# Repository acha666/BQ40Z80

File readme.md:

# BQ40Z80

一个简单的BQ40Z80 Demo板，~~绘制~~测试中

# 参考资料

* [bq4050从上电到PF](https://bq4050startup.vercel.app/)

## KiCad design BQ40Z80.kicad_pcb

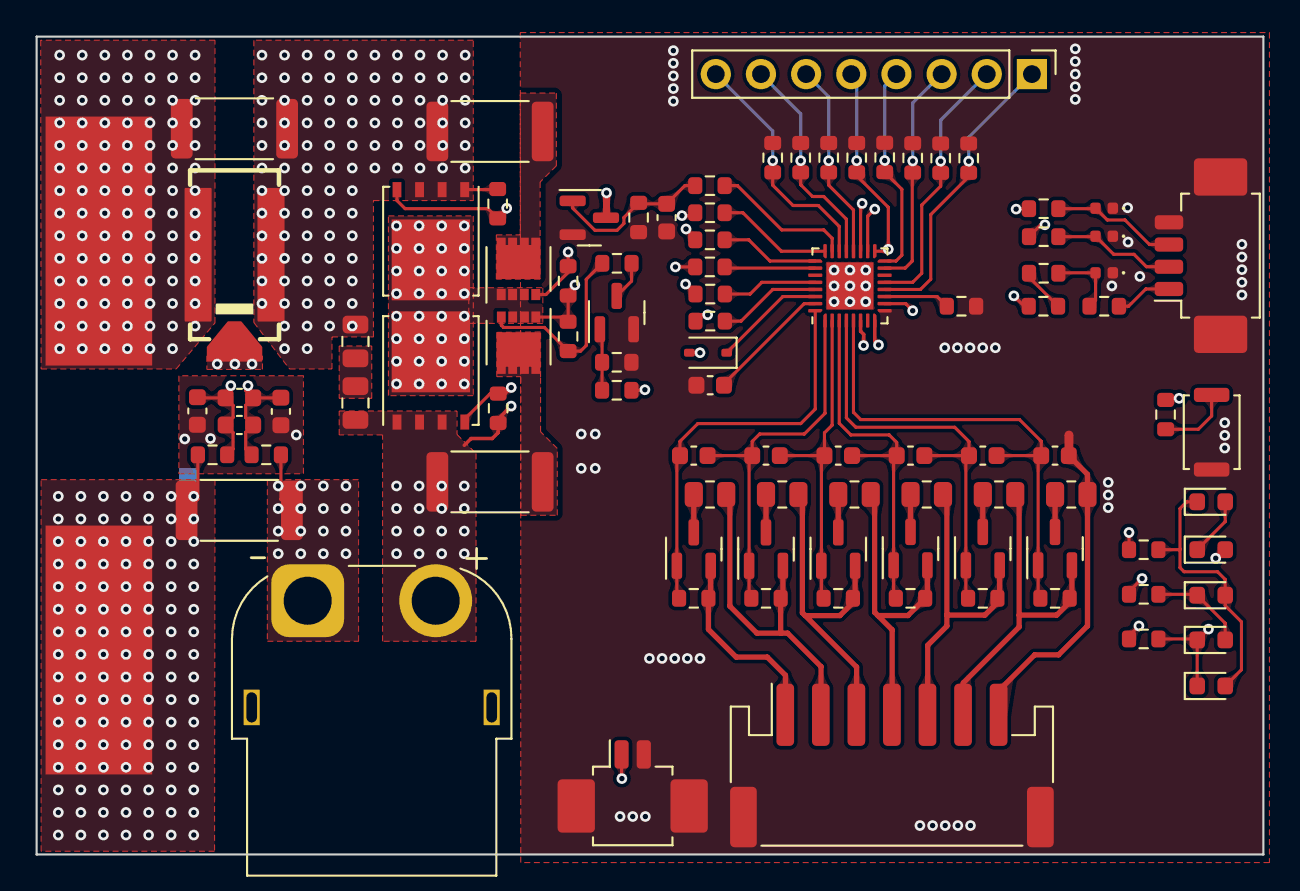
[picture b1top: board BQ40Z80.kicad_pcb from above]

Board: 4 copper layers, 69.0 x 46.0 mm, 97 parts (0 on the bottom side), 69 nets.

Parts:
C1, C2, C3, C4, C5, C6, C7, C13: 100nF; C_0603_1608Metric
C8: 2.2uF; C_0603_1608Metric
C9, C11: 100nF; C_0805_2012Metric
C10, C14: NC; C_0603_1608Metric
C12: 100pF; C_0603_1608Metric
D1: 1N5819WS; D_SOD-323
D2, D3, D4: D_TVS; D_0402_1005Metric
D5, D6, D7, D8, D9: LED; LED_0603_1608Metric
F1: SFK-3045; FUSE-SMD_3P-L9.5-W5.0
J1: Conn_01x02; Molex_PicoBlade_53261-0271_1x02-1MP_P1.25mm_Horizontal
J2: Conn_01x03; Molex_PicoBlade_53261-0471_1x04-1MP_P1.25mm_Horizontal
J3: Conn_01x07_MountingPin; JST_PH_S7B-PH-SM4-TB_1x07-1MP_P2.00mm_Horizontal
J4: Conn_01x08; PinHeader_1x08_P2.54mm_Vertical
J5: Conn_01x02_MountingPin; AMASS_XT60PW-F_1x02_P7.20mm_Horizontal
NT1: NetTie_2; NetTie-2_SMD_Pad0.5mm
NT2: NetTie_2; NetTie-2-234Layers_SMD_Pad0.5mm
Q1, Q2, Q3, Q4, Q5, Q6: AO3401A; SOT-23
Q7: DMN6075S; SOT-23
Q8, Q12: CSD18540Q5B; TDSON-8-1
Q9, Q10: AON6411; VSON-8_3.3x3.3mm_P0.65mm_NexFET
Q11: 2N7002; SOT-23
R1, R2, R3, R4, R5, R6: 43R; R_0805_2012Metric
R7, R8, R9, R10, R11, R12, R38, R49: 1K; R_0603_1608Metric
R13: 0R/NC; R_2512_6332Metric
R14, R15, R18, R19, R27: 5.1K; R_0603_1608Metric
R16, R20, R23, R25, R28, R30: 10M; R_0603_1608Metric
R17, R29: 100R/2W; R_2512_6332Metric
R21, R22, R26: 100R; R_0603_1608Metric
R24: 3mR; R_2512_6332Metric
R31, R32, R33, R34, R36, R37, R39, R40: 0R; R_0603_1608Metric
R35, R41, R42: 200R; R_0603_1608Metric
R43, R44, R45, R46, R47, R48: NC; R_0603_1608Metric
SW1: SW_Push; SW_Push_SPST_NO_Alps_SKRK
TH1: 10K@25°C; R_0603_1608Metric
TP1: BAT+; SolderWirePad_1x01_SMD_14x6mm
TP11: BAT-; SolderWirePad_1x01_SMD_14x6mm
U1: BQ40Z80RSMR; QFN-32-1EP_4x4mm_P0.4mm_EP2.65x2.65mm

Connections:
/0.0V: C6.2, J3.7, NT1.1, R6.2
/4.2V: J3.6, Q6.2 (S), R5.2, R12.1
/8.4V: J3.5, Q5.2 (S), R4.2, R11.1
/12.6V: J3.4, Q4.2 (S), R3.2, R10.1
/16.8V: J3.3, Q3.2 (S), R2.2, R9.1
/21.0V: J3.2, Q2.2 (S), R1.2, R8.1
/25.2V: J3.1, Q1.2 (S), R7.1
/BAT+: D1.2 (A), F1.1, R13.1, TP1.1
/CHG: R18.2, U1.29 (CHG)
/DISP: R46.2, SW1.1
/DSG: R27.2, U1.26 (DSG)
/FUSE: R15.2, U1.23 (FUSE)
/LEDCNTLA: D6.2 (A), D8.1 (K), D9.1 (K), R45.2
/LEDCNTLB: D7.1 (K), D8.2 (A), R44.2
/LEDCNTLC: D5.1 (K), D7.2 (A), D9.2 (A), R43.2
/PACK: R49.2, U1.25 (PACK)
/PACK+: C11.2, J5.2, Q12.1 (S), Q12.2 (S), Q12.3 (S), R29.2, R30.1, R49.1
/PACK-: J5.1, R24.2, R26.2
/PCHG: R19.2, U1.28 (PCHG)
/PDSG: Q11.1 (G), R28.2, R47.2
/PIN12: J4.1, R40.1, U1.12 (TS3/ADCIN1/GPIO)
/PIN13: J4.2, R34.1, U1.13 (~DISP/TS4/ADCIN2/GPIO)
/PIN15: J4.3, R39.1, R46.1, U1.15 (DISP/GPIO)
/PIN16: J4.4, R36.1, R47.1, U1.16 (PDSG/GPIO)
/PIN17: J4.5, R37.1, R48.1, U1.17 (~PRES/~SHUTDN/~DISP/PDSG/GPIO)
/PIN20: J4.6, R33.1, R45.1, U1.20 (LEDCNTLA/PDSG/GPIO)
/PIN21: J4.7, R32.1, R44.1, U1.21 (LEDCNTLB/GPIO)
/PIN22: J4.8, R31.1, R43.1, U1.22 (LEDCNTLC/GPIO)
/PRES: R35.1, R48.2
/SMBC: R41.1, U1.19 (SMBC)
/SMBD: R42.1, U1.18 (SMBD)
/SR_N: C12.2, C13.2, C14.2, R26.1, U1.6 (SRN)
/SR_P: C10.2, C12.1, C13.1, R22.1, U1.8 (SRP)
/TS1: J1.1, U1.10 (TS1)
/TS2: TH1.1, U1.11 (TS2)
/VC1: C5.2, C6.1, Q6.1 (G), R12.2, U1.5 (VC1)
/VC2: C4.2, C5.1, Q5.1 (G), R11.2, U1.4 (VC2)
/VC3: C3.2, C4.1, Q4.1 (G), R10.2, U1.3 (VC3)
/VC4: C2.2, C3.1, Q3.1 (G), R9.2, U1.2 (VC4)
/VC5: C1.2, C2.1, Q2.1 (G), R8.2, U1.1 (VC5)
/VC6: C1.1, Q1.1 (G), R7.2, U1.32 (VC6)
/VCC: R21.2, U1.24 (VCC)
GND: C7.2, C8.2, C10.1, C14.1, D2.1 (A1), D3.1 (A1), D4.1 (A1), J1.2, J1.MP (MountPin), J2.4, J2.MP (MountPin), J3.MP (MountPin), NT1.2, NT2.1, Q7.2 (S), Q11.2 (S), R14.2, R28.1, R31.2, R32.2, R33.2, R34.2, R36.2, R37.2, R39.2, R40.2, SW1.2, TH1.2, U1.9 (VSS), U1.33 (EP)
GNDPWR: NT2.2, R22.2, R24.1, TP11.1
unnamed: C9.1, F1.3, Q8.1 (S), Q8.2 (S), Q8.3 (S), R13.2, R16.1, R17.1
unnamed: C9.2, C11.1
unnamed: D1.1 (K), U1.30 (BAT)
unnamed: D2.2 (A2), R35.2, R38.1
unnamed: D3.2 (A2), J2.2, R41.2
unnamed: D4.2 (A2), J2.3, R42.2
unnamed: D5.2 (A), D6.1 (K)
unnamed: J2.1, R38.2
unnamed: Q1.3 (D), R1.1
unnamed: Q2.3 (D), R2.1
unnamed: Q3.3 (D), R3.1
unnamed: Q4.3 (D), R4.1
unnamed: Q5.3 (D), R5.1
unnamed: Q6.3 (D), R6.1
unnamed: F1.2, Q7.3 (D)
unnamed: C7.1, Q7.1 (G), R14.1, R15.1
unnamed: Q8.4 (G), R16.2, R18.1
unnamed: Q9.5 (D), R17.2
unnamed: Q9.4 (G), R19.1, R20.1
unnamed: Q10.5 (D), R29.1
unnamed: Q10.4 (G), R23.2, R25.2
unnamed: Q11.3 (D), R25.1
unnamed: Q8.5 (D), Q9.1 (S), Q9.2 (S), Q9.3 (S), Q10.1 (S), Q10.2 (S), Q10.3 (S), Q12.5 (D), R20.2, R21.1, R23.1
unnamed: Q12.4 (G), R27.1, R30.2
unnamed: C8.1, U1.31 (PBI)

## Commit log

2023-06-28 Add readme.md
